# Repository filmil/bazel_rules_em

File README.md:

<!-- SPDX-License-Identifier: Apache-2.0 -->

# hdlf_rules_em

Hermetic Bazel rules for the electromagnetic analysis of KiCad boards with
[openEMS](https://openems.de), an FDTD solver.
The build will turn a board's `.kicad_pcb` and its stackup into an openEMS
model, solve it, and give Touchstone S-parameter files and impedance and
TDR plots. A test will check them against limits per net or pair, such as
90 Ω ±15 % differential impedance for a USB pair.
Every tool comes from a Bazel toolchain, so nothing needs to be installed
on the machine, and two builds give byte-identical outputs.

It is part of the hdlf hardware rules, next to
[hdlf_rules_kicad](https://github.com/filmil/bazel_rules_kicad) and
[hdlf_rules_fab](https://github.com/filmil/bazel_rules_fab).

Only Linux x86_64 hosts are supported.

## Status

The openEMS toolchain, `kicad_em_model`, `kicad_em_sim` and `kicad_em_test`
are here: the four steps of https://github.com/filmil/bazel_rules_em/issues/1.

What works now:

* **`kicad_em_model`**: a board's nets as an openEMS model, read from the
  `.kicad_pcb` itself so that nets and ports keep the board's names. It
  writes the model as JSON, as CSXCAD geometry (`model.xml`) and as a
  picture, and runs no solver.
* **`kicad_em_sim`**: solves a model with openEMS, each port excited in
  turn, and writes the S-parameters (Touchstone), plots of |S|, input
  impedance and TDR, and a report. Each run takes a fixed number of time
  steps, so the same model gives the same bytes.
* **`kicad_em_test`**: checks a simulation against limits in a JSON file,
  per port or per differential pair: impedance (from the TDR), insertion
  loss, return loss and skew. It fails on a violation, and `expect_fail`
  makes a known-bad board's test pass only when its checks fail.
* **The openEMS toolchain** (`@hdlf_rules_em//em:toolchain_type`), with one
  tool, `openems`: a runner that solves a simulation script with openEMS
  d686f1d and CSXCAD 626b99f on CPython 3.12. It always runs openEMS's
  multithreaded engine with a fixed thread count, and removes the time
  stamps openEMS writes into its output, so two runs give the same bytes.
  The EM rules will use it; there is no public rule for it yet.
* `determinism_test` builds a target twice and fails if any output
  differs;
* `swap_test` builds targets with every tool swapped for a stub, and fails
  if any output was made without a toolchain tool.

### The openEMS wheels

PyPI has no CSXCAD or openEMS, and no Linux distribution ships the
post-VTK commits. So their Python wheels are built once, by
`bazel run //tools:openems_wheels -- --out=DIR`, in a manylinux_2_28
container pinned by digest (with podman, on the operator's machine), and
mirrored as the release `mirror-openems-d686f1d` of this repository,
together with the three source tarballs they are built from and the
licences of everything inside them. `requirements_lock.txt` pins each wheel
by its sha256. The wheels need glibc 2.28 or later on the host, as the
Python interpreter does.

### Slow tests

A target that runs the solver, and every test that depends on one, is
tagged `fdtd`; a test whose own run solves is also `size = "large"`.
`bazel test //...` leaves those out; `bazel test --config=fdtd //...` runs
only them, and CI runs that in a job of its own.

## Using it

There is no release yet; 0.0.1, below, will be the first.

`MODULE.bazel`:

```starlark
bazel_dep(name = "hdlf_rules_em", version = "0.0.1")
```

`.bazelrc`, while the module is only in the filmil registry:

```
common --registry=https://raw.githubusercontent.com/filmil/bazel-registry/main
common --registry=https://bcr.bazel.build
```

`BUILD.bazel`:

```starlark
load("@hdlf_rules_em//em:defs.bzl", "kicad_em_model", "kicad_em_sim", "kicad_em_test")

# The USB pair of a two-layer 1.6 mm board, from the connector to the
# microcontroller.
kicad_em_model(
    name = "usb_model",
    pcb = ":pcb",
    nets = ["USB_DP", "USB_DM", "GND"],
    ports = {"P1": "J1.A6", "P2": "J1.A7", "P3": "U1.18", "P4": "U1.17"},
    dielectrics = ["1.51mm 4.5 0.02"],
)

# Its S-parameters, impedance and TDR, from 100 MHz to 6 GHz in 100 MHz
# steps (a grid that starts at its step, which the TDR checks need). It
# runs the solver: tag it fdtd.
kicad_em_sim(
    name = "usb_sim",
    model = ":usb_model",
    f_start = "100MHz",
    f_stop = "6GHz",
    points = 60,
    tags = ["fdtd"],
)

# The pair against limits: 90 ohm +-15 % differential, loss, skew.
kicad_em_test(
    name = "usb_em_test",
    size = "small",
    limits = "usb_limits.json",
    sim = ":usb_sim",
    tags = ["fdtd"],
)
```

Every rule is in [docs/defs.md](docs/defs.md).

## Building

```sh
bazel build //...
bazel test //...
cd integration && bazel test //...
```

After changing a `.bzl` file, regenerate the documentation with
`bazel run //docs:update_docs`.
Format with `bazel run //tools:buildifier`, and check hermeticity with
`bazel run //tools:lint`.
The solver tests run with `bazel test --config=fdtd //...`.

## Releasing

The operator runs the `Tag and Release` workflow
(`.github/workflows/tag-and-release.yml`, `workflow_dispatch`).
It picks the next version from the conventional commits since the last
tag, makes the tag, the release and its source archive, and opens one
pull request on the filmil registry and one on the Bazel Central Registry.
It needs the repository secret `BCR_PUBLISH_TOKEN`.

None of the modules published here are published with any sort of guarantee
whatsoever. Use at your own risk.

See the overall description at the [project page][pp].

[pp]: https://hdlfactory.com/post/2025/09/29/getting-ready-for-the-brave-new-bazel-modules-world/

## Licenses

This repository is under the Apache License 2.0 (`LICENSE`).
The tools and libraries that the build downloads are listed here, with their
versions, sources and licenses.

| What | Version | Source | License |
|---|---|---|---|
| Go SDK (builds the helpers: the launcher, the swap test's stub and checker, the determinism comparer) | as rules_go 0.64.2 picks it | [go.dev/dl](https://go.dev/dl/), fetched by rules_go | BSD-3-Clause |
| CPython (runs the openEMS runner) | 3.12, as rules_python 2.4.6 picks it | [python-build-standalone](https://github.com/astral-sh/python-build-standalone), fetched by rules_python | PSF-2.0 |
| openEMS (the solver, in the `openems` wheel) | commit d686f1d, as 0.37.0.post20261024 | [thliebig/openEMS](https://github.com/thliebig/openEMS); wheel built by `//tools:openems_wheels`, mirrored as `mirror-openems-d686f1d` | GPL-3.0-or-later |
| CSXCAD (the geometry, in the `csxcad` wheel, and inside `openems`) | commit 626b99f, as 0.7.0.post20261021 | [thliebig/CSXCAD](https://github.com/thliebig/CSXCAD); as above | LGPL-3.0-or-later |
| fparser (inside both wheels) | commit 4b9c845 | [thliebig/fparser](https://github.com/thliebig/fparser); as above | LGPL-3.0-or-later |
| HDF5, libaec, TinyXML, Boost (inside the wheels, from AlmaLinux 8 and EPEL) | 1.10.5, 1.0.2, 2.6.2, 1.66.0 | the manylinux_2_28 image's package repositories | BSD-3-Clause-style (HDF5), BSD-2-Clause, Zlib, BSL-1.0 |
| numpy, h5py, matplotlib and their dependencies | as `requirements_lock.txt` pins them | PyPI | BSD-3-Clause (numpy, h5py), matplotlib's PSF-based licence, and theirs |

The licence texts of what the two wheels hold are in
`openems-wheels-licenses.tar`, an asset of the mirror release, beside the
exact sources the wheels are built from.

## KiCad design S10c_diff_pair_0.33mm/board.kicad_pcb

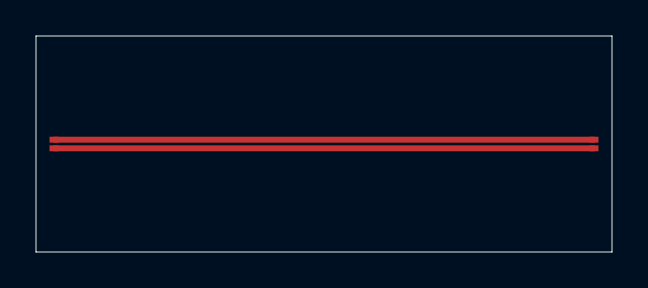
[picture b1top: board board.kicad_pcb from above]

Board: 4 copper layers, 32.0 x 12.0 mm, 4 parts (0 on the bottom side), 2 nets.

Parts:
J1, J2, J3, J4: Port

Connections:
DN: J3.1, J4.1
DP: J1.1, J2.1
